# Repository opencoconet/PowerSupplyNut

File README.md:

# PowerSupplyNut
Provides 5V, 1A for coconet

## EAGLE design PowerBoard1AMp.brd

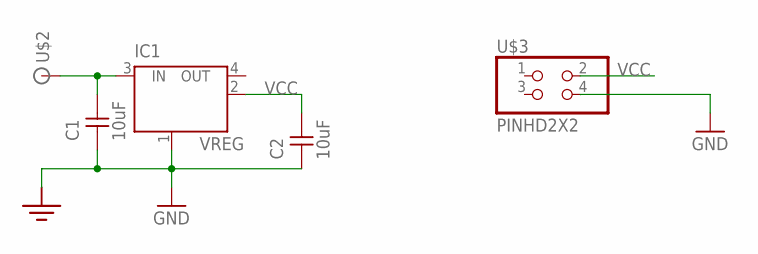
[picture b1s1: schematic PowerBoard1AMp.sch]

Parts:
C1, C2: 10uF; 1206
IC1: VREG; SOT223
U$1: GND; PAD.1
U$2: SIGNAL; PAD.1
U$3: PINHD2X2; 2X02SMD

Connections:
GND: C1.1, C2.1, IC1.1 (GND/ADJ), U$1.P$1, U$3.4
unnamed: C1.2, IC1.3 (IN), U$2.P$1
VCC: C2.2, IC1.2 (OUT), U$3.2

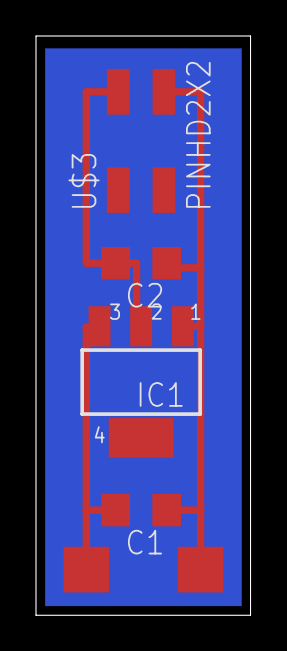
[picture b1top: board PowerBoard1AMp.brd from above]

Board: 2 copper layers, 11.9 x 32.2 mm, 6 parts (0 on the bottom side), 3 nets.

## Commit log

2015-07-30 README.md
2015-07-31 Adding schematic and board files
2015-07-31 Added two capacitors for regulators
2015-07-31 chaning the board boundry thickness
2015-07-31 Change the pins for VCC and GND in connector
